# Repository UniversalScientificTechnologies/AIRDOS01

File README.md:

# Airborne dosimeter device - AIRDOS

Cosmic radiation dosimeter unit. It is intended for airborne measurement of cosmic radiation and dosimetry in mixed ionization fields on board of aircraft. 

Technical parameters are following: 

* Silicon PIN diode detector with 60mm³ detection volume
* Measurement endurance 32 days
* Number of erengy channels    252
* Energy measurement resolution    <30 keV/channel
* GPS logging interval    5 minutes
* Time to GPS fix	26 s
* Airborne GPS parameters (Navigation altitude verified up to 36km amsl)
* Integration time    8 s
* Weight 1.225 kg (Without batteries and GPS antenna)

Device block diagram

CANDY detector schematics

The device is replaced with updated version [AIRDOS02](https://github.com/UniversalScientificTechnologies/AIRDOS02).

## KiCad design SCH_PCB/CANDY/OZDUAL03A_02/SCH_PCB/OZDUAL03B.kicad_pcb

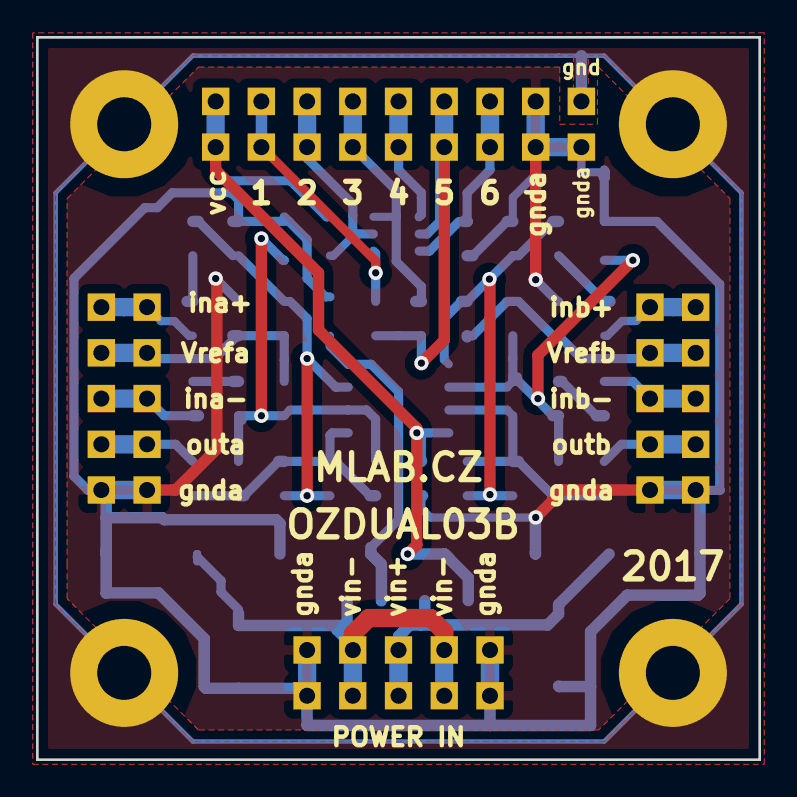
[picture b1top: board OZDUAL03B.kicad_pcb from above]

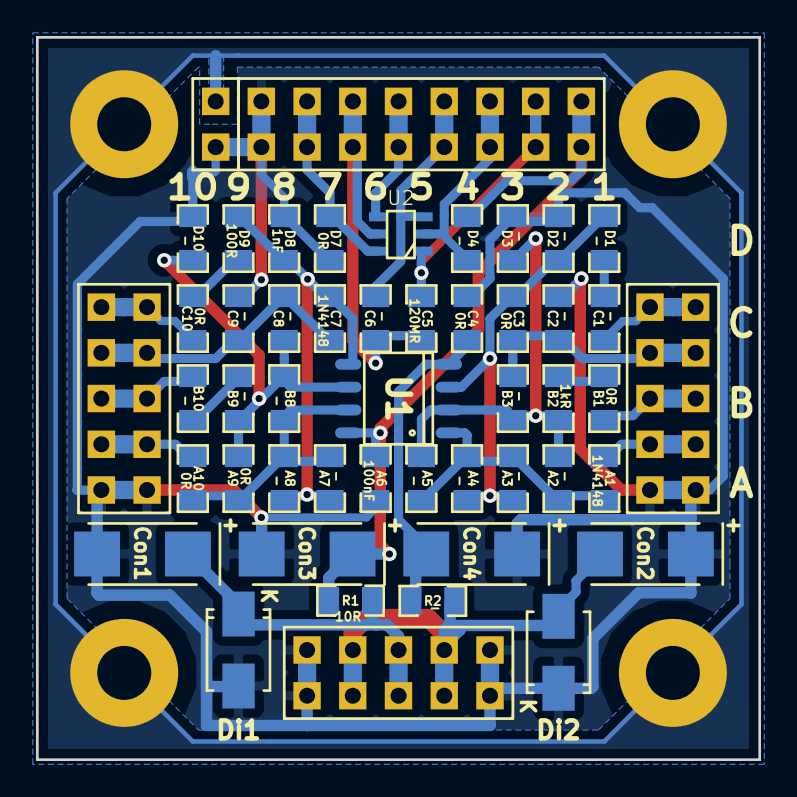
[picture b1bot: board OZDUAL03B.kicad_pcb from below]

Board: 2 copper layers, 40.1 x 40.1 mm, 53 parts (53 on the bottom side), 30 nets.

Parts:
A1: 1N4148; SMD-0805-hand-soldering
A2, A3, A4, A5, A7, A8: -; SMD-0805-hand-soldering
A6: 100nF; SMD-0805-hand-soldering
A9, A10: 0R; SMD-0805-hand-soldering
B1: 0R; SMD-0805-hand-soldering
B2: 1kR; SMD-0805-hand-soldering
B3, B8, B9, B10: -; SMD-0805-hand-soldering
C1, C2, C6, C8, C9: -; SMD-0805-hand-soldering
C3, C4, C10: 0R; SMD-0805-hand-soldering
C5: 120MR; SMD-0805-hand-soldering
C7: 1N4148; SMD-0805-hand-soldering
Con1, Con3: 47u; TantalC_SizeC_Reflow
Con2, Con4: -; TantalC_SizeC_Reflow
D1, D2, D3, D4, D10: -; SMD-0805-hand-soldering
D7: 0R; SMD-0805-hand-soldering
D8: 1nF; SMD-0805-hand-soldering
D9: 100R; SMD-0805-hand-soldering
Di1: M4; Diode-SMA_Standard
Di2: -; Diode-SMA_Standard
J1: JUMP2_2x1; Straight_2x01
J2: POWER; Straight_2x05
J3: OPAMPA; Straight_2x05
J4: OPAMPB; Straight_2x05
J5: SOT23-6; Straight_2x08
M1, M2, M3, M4: HOLE; MountingHole_3mm
R1: 10R; SMD-0805-hand-soldering
R2: -; SMD-0805-hand-soldering
U1: OPA2314; SO-8
U2: BSS138; SOT-23-6

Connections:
/1: C5.1, J5.13, J5.14, U2.1
/2: D4.2, J5.11, J5.12, U2.2
/3: C6.2, J5.9, J5.10, U2.3
/4: J5.7, J5.8, U2.4
/5: C5.2, C6.1, J5.5, J5.6, U2.5
/6: D7.1, J5.3, J5.4, U2.6
/INA+: C1.1, J3.1, J3.2
/INA-: B1.1, J3.5, J3.6
/INB+: C10.1, J4.1, J4.2
/INB-: B10.1, J4.5, J4.6
/OUTA: A1.1, J3.7, J3.8
/OUTB: A10.1, J4.7, J4.8
/VIN+: Con1.1, Di1.1, J2.5, J2.6, R1.2
/VIN-: Con2.2, Di2.2, J2.3, J2.4, J2.7, J2.8, R2.2
/VREFA: B3.2, C2.1, C3.2, J3.3, J3.4
/VREFB: C7.2, C8.2, C9.1, J4.3, J4.4
GND: J1.2, M1.1, M2.1, M3.1, M4.1
GNDA: A6.2, C2.2, C4.1, C9.2, Con1.2, Con2.1, Con3.2, Con4.1, D2.2, D3.2, D7.2, D8.1, D10.1, Di1.2, Di2.1, J1.1, J2.1, J2.2, J2.9, J2.10, J3.9, J3.10, J4.9, J4.10, J5.1, J5.2
unnamed: A1.2, A2.1, A3.2, A4.1, A5.2, U1.1
unnamed: A2.2, A5.1, B2.1, B3.1, D3.1, U1.2
unnamed: A3.1, A4.2, C3.1, D1.1, D2.1, U1.3
unnamed: A7.1, A8.2, C7.1, D8.2, D9.1, U1.5
unnamed: A9.2, B8.1, B9.1, C8.1, D10.2, U1.6
unnamed: A7.2, A8.1, A9.1, A10.2, B8.2, U1.7
unnamed: B1.2, B2.2
unnamed: B9.2, B10.2
unnamed: C1.2, D1.2
unnamed: C10.2, D9.2
VCC: A6.1, Con3.1, D4.1, J5.15, J5.16, R1.1, U1.8
VSS: C4.2, Con4.2, R2.1, U1.4

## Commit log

2017-03-31 Tvorba podkladů
2017-03-31 Schéma
2017-04-03 Improved documentation.
2017-04-03 Update README.md
    Image changed to real dosimetry photo.
2017-04-03 vykres OZDUAL03A
2017-04-03 White balance improved.
2017-04-03 Update README.md
    Adding reference to UST e-shop.
2017-04-03 New battery holder.
2017-04-04 Schemes
2017-04-04 Edit readme
2017-04-04 EDIT
2017-04-18 Edit schema
2017-08-16 Add files via upload
    circuit improvements.
2017-09-04 revise of schematic
2017-09-04 revise readme
2017-09-07 Improving documentation.
2017-09-07 Adding design of 3D printed shielding box.
2017-09-10 version for measurement CME at short fly
2017-09-11 Box for AIRDOS - without strenghtening crossbars.
2017-09-14 Battery holder
2017-09-14 flexbatter side grip overhang enabled.
2017-09-15 New schematics Candy
2017-09-15 Edit batter holder
2017-09-15 New stl
2017-10-06 Exchange the image
2017-10-06 Data editing
    update schema, new label
2017-10-09 New device labels.
2017-10-09 A QRcode label with link to documentation added.
2017-10-09 New suggestion for device label.
2017-10-11 Text graphics improvement.
2017-10-18 change schematics R11/D5 R12
2017-10-20 resizing of labels format.
2017-10-20 resizing to 18mm printing height.
2017-10-20 resizing to 18mm height
2017-10-21 Improving a quality of title schematics.
2017-10-21 Parameters correction in documentation.
2017-10-21 Improvement of commercial info.
2017-10-21 fix of a typo.
2017-10-21 Adding dosimeter photo with labels applied.
2017-10-21 new document describing device labeling
2017-10-25 more blinks for Dasa
2017-11-04 adding new photos of AIRDOS device.
2017-11-04 Device photo enhancement.
2017-11-27 AIRDOS5 with new GPS module, switch off GLONASS
2017-12-07 Version without SDcard for Moussala
2017-12-08 Draw scheme
2017-12-08 fryday version with one serial line
2018-01-21 Moussala FW
2018-01-21 FW for LET FIK3
2018-01-22 Renaming
2018-01-22 Readme schematics and PDF updated from KiCAD file.
2018-01-23 image path changed to relative
2018-04-17 new version with RTC instead of GPS
2018-04-22 missing comma in Csv
2018-04-24 lightning example was added
2018-05-18 some new test versions
2018-05-22 AIRDOS-F with lightning detector. This version stops integration after lightning.
2018-05-22 10 secands integration with lightning detection
2018-05-27 Tested delays for AIRDOS-F.
2018-06-01 calibrated version
2018-07-04 version for Santorini
2018-07-19 AIRDOS-F with offset compensation
2018-07-19 AIRDOS6 with AIRDOS-F HW and GPS
2018-07-31 repair of bug in offset measurement. Delay was added after analog mutiplexer switching.
2018-08-23 derived version AIRDOS-F for Musala without SDcard
2018-08-23 AirdosF for Musala is CANDY3
2018-09-07 Added datasheet of SD memory card used.
2018-09-21 forst atempt to read SN
2018-09-21 Id was added
2018-09-21 ble.c
2018-09-21 Id test
2018-09-25 introducing SN to logfile
2018-10-18 removed lightning detector from F version
2018-10-18 version for Trompier
2018-11-16 AIRDOS-G was added
2018-11-18 more power saving for AIRDOS_G, data logging only high fluxes
2018-11-19 debug version G version for Galapagos
2018-11-19 decrease noise sensitivity for online flux calculation and recording decision
2018-11-19 nevim
2018-11-19 description of libraries and IDE versions used for compilation
2018-12-10 flight from Galapagos islands
2018-12-14 New QRcode label and generating script.
2018-12-14 Link QRcode image
2018-12-14 Regeneratig output files.
2018-12-14 Changing link and regenerating files.
2019-01-14 Doplneni gitignore
2019-01-23 before flight from HIMAC form Japan
2019-01-29 New labels added - 006 til 017
2019-02-07 Divisek for Dasa for lightning test at Mikes's generator
2019-03-26 AIRDOS CG for a trip around the World in 2019
2019-04-02 AIRDOS G with fixed offset
2019-04-04 we added Fik4
2019-04-04 fik4 removed
2019-07-08 New RTC library for AIRDOS F
2019-07-08 new githash
2019-07-09 removed dynamic offset correction
2019-07-09 RTC error correction in AIRDOS G
2019-07-30 In AIRDOS G was added timestamp from RTC after last NMEA message
2019-10-23 correct spelling of constant
2019-12-16 Trompier
